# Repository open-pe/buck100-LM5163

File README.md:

## Specs

|      |          |
|------|----------|
| Vin  | 6..100 V |
| Vout | 2..20 V  |
| Iout | 0.5 A    |
| fsw  | 100 kHz  |

## Feedback Resistor and Indcutor Values

Use the table to find values for Rfb1, Rfb2, Rt, Ra and inductivity for given V_out at ~100khz switching frequency:

| Vout |      | Rfb1 | Rfb2 | Rt   | Ra (R4)    | L     |
|------|------|------|------|------|------------|-------|
| 3.33 |      | 390k | 220k | 100k | 470k..715k | 470uH | 
| 3.35 |      | 430k | 240k | 100k | 470k..715k | 470uH |
| 11.2 |      | 470k | 56k  | 390k | 600k..1.5M | 1.6mH |
| 11.3 |      | 430k | 51k  | 390k | 600k..1.5M | 1.6mH |
| 11.3 |      | 430k | 50k  | 390k | 600k..1.5M | 1.6mH |

* [Common Resistor Values](https://ch00ftech.com/wp-content/uploads/2012/05/resistorsandcaps.pdf)
* LM218x Excel Tool: [Quickstart Calculator](https://www.ti.com/tool/LM5163-LM5164DESIGN-CALC)

## Assembly diagrams

Footprints with the value to place on each, one diagram per variant. Orange boxes differ between
variants, blue boxes are the same on both. L1 and C2 sit on the bottom side; the right half of each diagram
shows that side seen from below. "1" marks pin 1 of U2 and J1, "+" marks the plus pad of the C2 elko.
J1 pinout: 1 = Vout, 2 = GND, 3 = Vin.

The variant values come from the table above (first row of each voltage). The schematic still carries
33k/10k for R1/R2 (Vout ≈ 5.2 V) and 100uH for L1, so do not build from the schematic BOM or the iBOM.

### 3.3 V

### 11 V

Regenerate after a layout or value change with KiCad's Python:
`/Applications/KiCad/KiCad.app/Contents/Frameworks/Python.framework/Versions/Current/bin/python3 assembly/gen_assembly_diagram.py`

## LM516x features

* [LM5163](https://www.ti.com/lit/ds/symlink/lm5163.pdf) (.5A) LM5164](https://www.ti.com/lit/ds/symlink/lm5164.pdf) (
  1A)
* sync buck with nearly 100% max duty cycle
* 0.725Ω NFET buck switch, 0.34Ω NFET synchronous rectifier
* constant on-time (COT) control architecture
* light-load power saving mode
* 10.5µA no-load input quiescent current
* soft-start, UVLO, thermal shutdown
* PGOOD indicator
* quick start calc: https://www.ti.com/tool/LM5163-LM5164DESIGN-CALC

## Pin-compatible chips

| MPN          | Vi  | Io   | NFET Rds  | Iq    |                  | Light-Load |                                                                   |
|--------------|-----|------|-----------|-------|------------------|------------|-------------------------------------------------------------------|
| LM5168       | 120 | 0.3  | 1.9/.71Ω  | 10µA  | COT, FPWM or PFM | DEM        | [pdf](https://www.ti.com/lit/ds/symlink/lm5169.pdf)               |
| LM5169       | 120 | 0.65 | 1.9/.71Ω  | 10µA  | COT, FPWM or PFM | DEM        | [pdf](https://www.ti.com/lit/ds/symlink/lm5169.pdf)               |
| LM5163       | 100 | 0.5  | .725/.34Ω | 10µA  | COT              | DEM        | https://www.ti.com/lit/ds/symlink/lm5163.pdf?ts=1731081870545     |
| LM5164       | 100 | 1.0  | .725/.34Ω | 10µA  | COT              | DEM        | https://www.ti.com/lit/ds/symlink/lm5163.pdf?ts=1731081870545     |
| LM5017       | 100 | 0.6  |           |       | COT              |            |                                                                   |
| LM34927      |     |      |           |       |                  |            |                                                                   |
| *TPP00031/2* | 100 | 0.3  | .7/.3Ω    | 125µA | pulse skip       |            | [pdf](https://static.3peak.com/res/doc/ds/Datasheet_TPP0003x.pdf) |

* [WEBENCH Power Designer]( https://webench.ti.com/power-designer/switching-regulator?base_pn=LM5163&origin=ODS&litsection=features)
* https://webench.ti.com/power-designer/switching-regulator/select

## inductors

requirements:

* Isat well above current limit setting
* Isat decreases with rising temperature
* refer to datasheet [pg 18](https://www.ti.com/lit/ds/symlink/lm5163.pdf#page=18)

|                      | L     | Isat(30%) | DCRmΩ(max) | Q         | px(250) | size | Notes                                                                                           |
|----------------------|-------|-----------|------------|-----------|---------|------|-------------------------------------------------------------------------------------------------|
| MSS1260-124KL        | 120uH | 2A        | 195        |           | 1,33€   | 12mm | LM5163 datasheet                                                                                |
| Bourns SRN6045-101M  | 100uH | .7A       | 494        | 22@796kHz | $,27    | 6mm  |                                                                                                 |
| VLS5045EX-101M       | 100uH | .7A       | 754        |           | $,20    | 5mm  | ordered                                                                                         |
| → TY NRS8040T101MJGK | 100uH | 1.1A      | 364        |           | $,22    | 8mm  | [pdf](https://mm.digikey.com/Volume0/opasdata/d220001/medias/docus/2544/NRS8040T101MJGK_SS.pdf) |
| IFSC3232DBER471M02   |       |           |            |           |         |      |                                                                                                 |
|                      |       |           |            |           |         |      |                                                                                                 |

## Other designs using same chip

* https://github.com/90wishpack/LM5164
* https://github.com/FarwayDot/Adapter_PowerSupply_Vigi

# Tests

```
3.3V version:
Vin=15
no load: voltage can oscillate arround 3.3V
750Ω load: voltage stable
short circuit: 50mA Iin
```

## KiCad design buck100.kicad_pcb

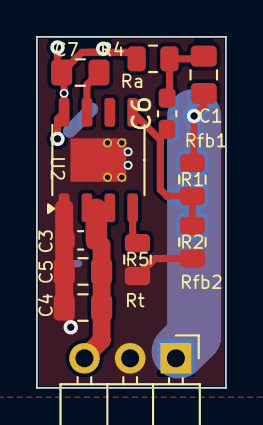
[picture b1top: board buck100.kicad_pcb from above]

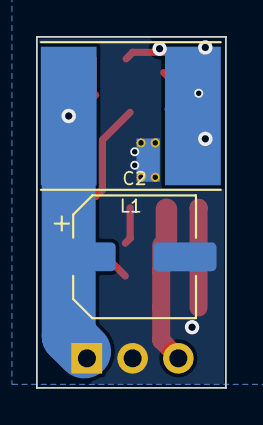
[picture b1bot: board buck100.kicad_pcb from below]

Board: 2 copper layers, 10.5 x 19.5 mm, 14 parts (2 on the bottom side), 8 nets.

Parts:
C1: 2200 pF, 100 V; C_0805_2012Metric_Pad1.18x1.45mm_HandSolder
C2: 22uF, 25V, X7R; CP_Elec_6.3x5.9
C3: 220nF, 100V, X7S; C_0603_1608Metric_Pad1.08x0.95mm_HandSolder
C4, C5: 1uF, 100V, X7S; C_0805_2012Metric_Pad1.18x1.45mm_HandSolder
C6: 56pF, 50V; C_0603_1608Metric_Pad1.08x0.95mm_HandSolder
C7: 2200 pF, 50 V; C_0805_2012Metric_Pad1.18x1.45mm_HandSolder
J1: Conn_01x03_Male; PinHeader_1x03_P2.54mm_Horizontal
L1: 100uH; L_Taiyo-Yuden_NR-80xx_HandSoldering
R1: 33k; R_0805_2012Metric
R2: 10k; R_0805_2012Metric
R4: R_0805_2012Metric
R5: 100k; R_0805_2012Metric
U2: LM5163DDAR; HSOP-8-1EP_3.9x4.9mm_P1.27mm_EP2.41x3.1mm_ThermalVias

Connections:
+3.3V: C1.2, C2.1, J1.1, L1.2, R1.1
FB: C6.1, R1.2, R2.1, U2.5 (FB)
GND: C2.2, C3.2, C4.2, C5.2, J1.2, R2.2, R5.2, U2.1 (GND), U2.9 (EP)
unnamed: C1.1, C6.2, R4.2
unnamed: C7.1, U2.7 (BST)
unnamed: R5.1, U2.4 (RON)
SW: C7.2, L1.1, R4.1, U2.8 (SW)
VIN: C3.1, C4.1, C5.1, J1.3, U2.2 (VIN), U2.3 (EN/UVLO)

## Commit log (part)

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2024-10-30 initial
2024-10-30 readme
2024-10-30 add 3d rendering
2024-12-05 docs, vias
2024-12-19 minor changes
2024-12-24 config table
2025-09-14 resistor values
2025-09-24 feedback resistors list
2025-09-25 bump kicad version
2025-10-23 ignore ibom
2025-10-29 set drill origin
